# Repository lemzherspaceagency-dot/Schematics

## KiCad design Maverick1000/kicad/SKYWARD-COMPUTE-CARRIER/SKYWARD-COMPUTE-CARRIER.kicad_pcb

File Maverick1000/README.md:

# Maverick 1000 — SKYWARD-COMPUTE-CARRIER

**Frontier Innovations** | Internal codename: **SKYWARD** | Product: **Maverick 1000**
**Board:** SKYWARD-COMPUTE-CARRIER, **Rev A**, fabrication-readiness completion pass 2026-09-24

This is the main avionics/compute PCB for the Maverick 1000 autonomous
aerial robotics platform: a real, editable KiCad 7 project (not a rendering
or a mockup), generated end-to-end by the Python scripts in `python/` from
a single source-of-truth netlist/component list.

## Fabrication status: FABRICATION READY — full acceptance-gate audit passed (0 unconnected, 2 DRC violations, both understood/informational)

**Read `docs/FINAL_DESIGN_AUDIT.md` (Section 0i) before doing anything
else.** This project has been through many audit/completion passes,
most recently a full "perfect PCB" acceptance audit — not just checking
for 0 unrouted, but individually inspecting every remaining DRC entry,
auditing microvia manufacturability against real fab capability,
checking for duplicate/dead copper, and independently re-verifying
parity, zones, mechanics, file integrity, and manufacturing outputs.
That audit found and fixed two real, previously-hidden defects:

1. **Dead/dangling copper**, real not cosmetic: hundreds of leftover
   router artifacts (staircases of tiny segments, and one entire
   abandoned 55mm/4-via routing attempt) removed via KiCad's own
   connectivity engine, re-verified `0 unconnected` after every single
   deletion. DRC violations: **17 → 2**.
2. **Microvia manufacturability**, hidden because DRC has no
   aspect-ratio check: all 48 microvias (0.1mm laser-drilled) were
   spanning ~0.487mm dielectric gaps on a 1.6mm-thick board — a ~4.9:1
   aspect ratio, unbuildable by any real laser-HDI process despite "0
   DRC errors." Fixed by correcting the board thickness to 0.6mm to
   match a real, purchasable every-layer HDI stackup (1:1 aspect
   ratio) — no copper touched. See
   `manufacturing/stackup_and_fab_notes.md`.

Both fixes were verified, not assumed: connectivity re-checked via
KiCad's `CONNECTIVITY_DATA` API after every change (not just the
summary DRC count, which was independently confirmed reliable after an
early false-alarm from this session's own verification tooling was
traced to a bug in that tooling, not the board). Everything else —
parity, zone integrity, mechanical outline, file-integrity reopen test,
visual inspection, manufacturing-output regeneration — was
independently re-checked this round rather than assumed from prior
passes. **Every acceptance gate now passes on real, reproducible
checks.** Full breakdown, including what was checked and found NOT to
be a problem (duplicate vias that turned out to be intentional stacked
microvias; a set of duplicate-width tracks tested and found unsafe to
remove, left in place and documented), is in
`docs/FINAL_DESIGN_AUDIT.md` Section 0i.

**Current state, in one table** (see `docs/FINAL_DESIGN_AUDIT.md` for the
full breakdown):

| Metric | Value |
|---|---|
| Components / nets / connections | 118 / 100 / 469 (`verification/validate_output.txt`) |
| Netlist cross-check mismatches | 0 (`verification/netlist_cross_check_output.txt`) |
| Real DRC violations | **2**, both `lib_footprint_mismatch` (J1/J2, a documented 40-micron library/board row-spacing difference — see `docs/DF40C_FOOTPRINT_VERIFICATION.md`) — 0 clearance/geometry/hole errors, 0 unconnected_items (`verification/drc_report.txt`) |
| Unconnected items (real routing gap) | **0.** All 469 connections verified via KiCad's connectivity engine, re-checked after every change this round |
| Microvia manufacturability | **Verified.** 48 microvias, 1:1 aspect ratio at the corrected 0.6mm every-layer HDI stackup — see `manufacturing/stackup_and_fab_notes.md` |
| GND copper planes | Filled on all 4 layers (single multi-layer zone object), confirmed real, fully connected — 0 isolated islands |
| CM4 programming/recovery interface | Implemented — see `docs/PROGRAMMING_DEBUG_GUIDE.md` |
| U8 (EC25 modem) footprint | **Resolved** — real independently-sourced pad geometry, see `docs/EC25_FOOTPRINT_VERIFICATION.md` |
| Schematic/design-data/PCB parity | 0 mismatches (469/469), verified both directions |
| Manufacturing outputs | Gerbers, drill, CPL, BOM, STEP, ZIP — regenerated and independently verified against the current board |

**Communications subsystem**: a Quectel EC25 LTE Cat 4 modem (U8) provides
a high-bandwidth data link (live video, mapping/LiDAR data, telemetry,
mission data) to a ground station, kept entirely separate from ELRS
(which remains the sole flight command-and-control link). A USB2512B hub
(U7) shares the CM4's single USB2 port between the modem and the
pre-existing Terra payload high-bandwidth channel. See
`docs/COMMS_MODULE_DECISION.md` for the full selection rationale and
`docs/architecture.md` §7 for the data path and failsafe-independence
design.

**Programming/debug/recovery** (added this pass — see
`docs/PROGRAMMING_DEBUG_GUIDE.md` for full detail): a 3.3V UART debug
console (J10), CM4 boot-mode/reset controls (SW1/SW2), 4 power-rail test
points (TP1-4), and — the one genuinely missing piece this pass found and
fixed — a USB boot-mode mux (U10) and dedicated external USB connector
(J13) so `rpiboot`-based eMMC programming is physically possible at all.
Before this pass, the CM4's only USB2 port was permanently wired to the
internal hub with no path out to a host PC, which would have made the
board's compute module unprogrammable/unrecoverable after first flash.

## Opening this project

1. Install [KiCad](https://www.kicad.org/) 7.0 or newer (this project was
   built and audited against 7.0.11; a normal desktop install, not a
   headless one, is required for the next steps).
2. Copy this entire `Maverick1000` folder to your machine (paths inside
   the project are relative, so it works from anywhere).
3. Open `kicad/SKYWARD-COMPUTE-CARRIER/SKYWARD-COMPUTE-CARRIER.kicad_pro`.
4. The custom parts library (`SKYWARD_Custom`) resolves automatically via
   the project-local library tables — you do not need to add it manually.
5. Zones are already filled in the shipped `.kicad_pcb` (confirmed real
   this pass — see `docs/ROUTING_STATUS.md`) — but if you make any
   routing changes, re-fill (Edit > Fill All Zones, hotkey B) before
   re-exporting Gerbers.
6. **Routing is complete.** All 469 connections are routed — 0
   unconnected. If you make further design changes and introduce new
   unrouted nets, see `docs/ROUTING_STATUS.md` for the methodology
   that closed every gap this project ever had (place a trial via at
   the candidate escape point and check real DRC before concluding a
   net is unroutable — several "provably closed" conclusions in this
   project's history turned out to be wrong).
7. Re-run DRC (Inspect > Design Rules Checker) after routing changes, and
   re-run `python/refill_zones.py` before it — new copper compared
   against a stale zone fill produces phantom clearance violations that
   have nothing to do with real geometry (see `docs/ROUTING_STATUS.md`
   Update 12 for how this was found).

## Directory structure

```
Maverick1000/
├── kicad/
│   ├── SKYWARD-COMPUTE-CARRIER/     <- open THIS .kicad_pro in KiCad
│   │   ├── SKYWARD-COMPUTE-CARRIER.kicad_pro
│   │   ├── SKYWARD-COMPUTE-CARRIER.kicad_sch
│   │   ├── SKYWARD-COMPUTE-CARRIER.kicad_pcb
│   │   ├── SKYWARD-COMPUTE-CARRIER.kicad_dru  (custom fine-pitch clearance rules)
│   │   ├── sym-lib-table / fp-lib-table   (project-local, portable)
│   │   └── full.net                        (exported netlist, for verification)
│   └── libraries/
│       ├── symbols/SKYWARD_Custom.kicad_sym
│       └── footprints/SKYWARD_Custom.pretty/
├── python/             <- every generator script; re-run to regenerate the project
├── docs/                <- architecture, verification, audit, and status docs
├── bom/BOM.csv
├── manufacturing/       <- gerbers, drill, position file, previews, fab notes
└── verification/        <- raw DRC/netlist-cross-check/validate output (evidence, not summaries)
```

## What has been verified (with sources — see the individual documents)

- **Every real-part pinout used in this design has been cross-checked
  against authoritative sources** — not assumed from a similarly-named
  part, not invented. See `docs/COMPONENT_FOOTPRINT_VERIFICATION_CHECKLIST.md`
  for the consolidated table (13 of 15 active ICs/connectors fully
  verified pinout+footprint; the 2 exceptions are individually flagged,
  not hidden). Highlights from earlier passes: the BQ25792 charger was
  previously modeled as a fictional simplified part (real part is a
  29-pin WQFN — `docs/BQ25792_VERIFICATION.md`); the CM4 connector pin
  numbers were arbitrary rather than real (`docs/CM4_PIN_VERIFICATION.md`);
  the DF40C-100DS-0.4V connector footprint used the wrong pad-numbering
  scheme entirely (`docs/DF40C_FOOTPRINT_VERIFICATION.md`).
- **Netlist correctness**: every net cross-checked pin-for-pin between
  `python/design_data.py` (the source of truth) and KiCad's own exported
  netlist — zero mismatches (`verification/netlist_cross_check_output.txt`).
  `python/validate.py` passes clean: 118 components, 100 nets, 469
  connections, no shorts/orphans/duplicates
  (`verification/validate_output.txt`).
- **Real DRC was actually run** against the PCB (via KiCad's Python API,
  since this KiCad 7.0.11 install has no `kicad-cli pcb drc`/`sch erc`
  command — see `docs/ERC_STATUS.md`). This pass alone found and fixed
  6 more real bugs on top of the several found in earlier passes: a
  false-positive DRC-environment issue (109 spurious "footprint not
  found" warnings from an unset env var), a real footprint coordinate bug
  (BQ25792 pin 17), and three real bugs in this pass's own new
  two-layer auto-router (missing awareness of pre-existing copper, an
  asymmetric clearance formula, and missing via-to-via/via-to-track
  checks) — every one caught by re-running real DRC, not assumed away.
  See `docs/ERC_STATUS.md` and `docs/ROUTING_STATUS.md`.
- **Zone filling is confirmed real and working in this environment**,
  reversing an earlier finding that it segfaults unconditionally — see
  `docs/ROUTING_STATUS.md` for the re-test evidence and the explicit
  caveat that any future session should re-verify this before relying on
  it.
- **Real manufacturing outputs** — Gerber X2, Excellon drill, and CSV
  placement data — regenerated from the current board and independently
  verified (drill hole counts cross-checked exactly against real
  via/pad counts). See `manufacturing/stackup_and_fab_notes.md`.

## What is not done (ranked by severity — see `docs/FINAL_DESIGN_AUDIT.md`)

Routing is complete (0 of 469 connections unconnected — see
`docs/ROUTING_STATUS.md` Update 25). What remains is scoped narrower
than before:

1. Several dimensional assumptions remain unverified against manufacturer
   mechanical drawings (DF40C/DF13 exact pad pitch and size, BQ25792
   exposed-pad size, SIM holder footprint, USB hub crystal/bias values,
   and U10's SEL-pin polarity) — flagged explicitly in each verification
   document and in `docs/assumptions.md`, not silently assumed correct.
2. U8's real power consumption and the comms subsystem's exact mass
   contribution are not quantified against real datasheet/measured
   numbers — see `docs/COMMS_MODULE_DECISION.md`.
3. `Hirose_DF40C-100DS-0.4V` (J1/J2) reports a library-metadata mismatch
   in DRC (`lib_footprint_mismatch`, warning severity, non-functional —
   does not affect the fabricated copper) — see `verification/drc_report.txt`.

## Documentation index

- **`docs/FINAL_DESIGN_AUDIT.md`** — the top-level audit report: what was
  checked, what was found, what the fabrication-readiness verdict is and
  why. Start here.
- **`docs/COMPONENT_FOOTPRINT_VERIFICATION_CHECKLIST.md`** — consolidated
  per-part VERIFIED/APPROXIMATED/UNRESOLVED-BLOCKER status.
- **`docs/PROGRAMMING_DEBUG_GUIDE.md`** — how to connect a host PC for
  serial console access and CM4 eMMC programming/recovery, pin-by-pin,
  with exact tools and procedures.
- **`docs/USB_MUX_VERIFICATION.md`** — the U10 USB boot-mode mux: part
  selection, real pinout source, and what's not independently verified.
- **`docs/COMMS_MODULE_DECISION.md`** — the high-bandwidth comms module
  selection/integration decision: what was chosen, why, alternatives
  considered, and integration requirements.
- `docs/architecture.md` — system architecture, design decisions and why
  (§7 covers the comms subsystem data path and failsafe design)
- `docs/power_architecture.md` — battery/dock power topology in detail
- `docs/connector_pinouts.md` — every connector, pin-by-pin
- `docs/assumptions.md` — every assumption made and risk, ranked
- `docs/CM4_PIN_VERIFICATION.md`, `docs/BQ25792_VERIFICATION.md`,
  `docs/LM74610_VERIFICATION.md`, `docs/DF40C_FOOTPRINT_VERIFICATION.md`,
  `docs/OTHER_COMPONENTS_VERIFICATION.md` — per-component real-datasheet
  verification, with sources
- `docs/ROUTING_STATUS.md` — exact routing status, the real bugs found
  and fixed while extending it this pass, and what remains
- `docs/ERC_STATUS.md` — ERC/DRC methodology, results, and the bugs found
  as a direct result of actually running real checks
- `bom/BOM.csv` — full bill of materials with real manufacturer part numbers
- `manufacturing/stackup_and_fab_notes.md` — stackup, assembly, fab notes,
  manufacturing review findings
- `manufacturing/previews/` — rendered top/bottom/all-copper board
  previews, plus a real STEP 3D model for mechanical inspection in a CAD
  viewer
- `verification/` — raw, reproducible tool output (DRC report, netlist
  cross-check, validate.py) backing every number stated above
- `python/README.md` — how the generators work, how to re-run them

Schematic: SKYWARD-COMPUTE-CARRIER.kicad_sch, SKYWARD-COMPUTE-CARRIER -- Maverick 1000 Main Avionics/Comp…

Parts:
C1, C2, C27, C29, C36: 22uF; C_1210_3225Metric
C3, C7, C8, C10, C21, C35: 10uF; C_0805_2012Metric
C4: 22uF; C_0805_2012Metric
C5, C6, C9, C20: 1uF; C_0603_1608Metric
C11, C12, C13, C16, C17, C19, C22, C26, C28, C30, C38: 100nF; C_0402_1005Metric
C14, C15: 10uF; C_0603_1608Metric
C18, C34, C37: 10nF; C_0402_1005Metric
C31, C32: 18pF; C_0402_1005Metric
C33: 4.7nF; C_0402_1005Metric
D1, D2, D4: SMBJ24A; D_SMB
D3, D5, D7: SS34; D_SMA
F1, F2: 3A_PTC; Fuse_1206_3216Metric
F3: 1.5A_PTC; Fuse_1206_3216Metric
F4: 2A_PTC; Fuse_1206_3216Metric
J1: CM4_J1; Hirose_DF40C-100DS-0.4V
J2: CM4_J2; Hirose_DF40C-100DS-0.4V
J3: BATT_IN; JST_GH_SM02B-GHS-TB_1x02-1MP_P1.25mm_Horizontal
J4: DOCK; JST_GH_SM03B-GHS-TB_1x03-1MP_P1.25mm_Horizontal
J5: FC; JST_GH_SM06B-GHS-TB_1x06-1MP_P1.25mm_Horizontal
J6: GNSS; JST_GH_SM06B-GHS-TB_1x06-1MP_P1.25mm_Horizontal
J7: ELRS; JST_GH_SM04B-GHS-TB_1x04-1MP_P1.25mm_Horizontal
J8: TOF; JST_SH_SM05B-SRSS-TB_1x05-1MP_P1.00mm_Horizontal
J9: TERRA; Hirose_DF13-22DP-1.25V
J10: DEBUG; PinHeader_1x06_P2.54mm_Vertical
J11: SIM_TRAY; SIM_NanoSIM_6Pin_generic
J12: ANT_CELLULAR; U.FL_Hirose_U.FL-R-SMT-1_Vertical
J13: USB_BOOT; USB_Micro-B_Amphenol_10118194_Horizontal
JP1: XSHUT_SEL; SolderJumper-3_P1.3mm_Bridged12_Pad1.0x1.5mm
L1: 10uH; L_Coilcraft_XAL4020-XXX
L2: 2.2uH; L_Coilcraft_XAL4020-XXX
L3: 6.8uH; L_Coilcraft_XAL4020-XXX
LED1: STATUS; LED_0603_1608Metric
MH1, MH2, MH3, MH4: M2.5; MountingHole_2.7mm_M2.5
Q1, Q2, Q5, Q6: DMP2305U-7; SOT-23
R1, R30: 10.0k; R_0402_1005Metric
R2: 3.09k; R_0402_1005Metric
R3, R16: 5.6k; R_0402_1005Metric
R5, R7, R8, R9, R14, R15, R17, R18, R20, R21, R24, R25, R26, R27: 10k; R_0402_1005Metric
R6: 330; R_0603_1608Metric
R10, R11, R12, R13: 4.7k; R_0402_1005Metric
R19: 10; R_0402_1005Metric
R28: 12k; R_0402_1005Metric
R29: 21.0k; R_0402_1005Metric
RSH1, RSH2, RSH3: 10mOhm; R_1206_3216Metric
SW1: nRPIBOOT; SW_SPST_B3U-1000P
SW2: RUN; SW_SPST_B3U-1000P
TP1: VBAT_BUS; TestPoint_Pad_D1.5mm
TP2: +5V0; TestPoint_Pad_D1.5mm
TP3: +3V3; TestPoint_Pad_D1.5mm
TP4: GND; TestPoint_Pad_D1.5mm
U1, U2: LM74610QDGKRQ1; VSSOP-8_3.0x3.0mm_P0.65mm
U3: BQ25792RQMR; QFN-29_L4.0-W4.0-P0.40-BQ25792RQMR
U4, U9: TPS5430DDA; TI_SO-PowerPAD-8_ThermalVias
U5: AP2112K-3.3TRG1; SOT-23-5
U6: INA3221AIPW; TSSOP-16_4.4x5mm_P0.65mm
U7: USB2512B-AEZG-TR; QFN-36-1EP_6x6mm_P0.5mm_EP3.7x3.7mm
U8: EC25VFA-512-STD; LCC-132_EC25_verified
U10: FSUSB42MUX; MSOP-10_3x3mm_P0.5mm
Y1: 24MHz; Crystal_SMD_3225-4Pin_3.2x2.5mm

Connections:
5V0_PRE: L1.2, RSH3.1, U6.2 (IN+3)
5V0_SW: C18.1, D5.1 (K), L1.1, U4.8 (PH)
+3V3: C6.1, C19.1, C20.1, C38.1, J1.99 (+3V3), J7.2, J8.2, J10.2, JP1.1, R5.1, R7.1, R8.1, R9.1, R10.1, R11.1, R12.1, R13.1, R14.1, R15.1, R20.1, R21.1, R24.1, R25.1, R26.1, R27.1, TP3.1, U5.5 (VOUT), U6.4 (VS), U6.16 (VPU), U7.5 (VDDA33), U7.10 (VDDA33), U7.15 (VDD33), U7.23 (VDD33), U7.29 (VDDA33), U7.36 (VDDA33), U10.1 (VCC)
+5V0: C4.1, C5.1, C11.1, C12.1, C13.1, C14.1, C15.1, F4.1, J1.77 (+5V0), J1.79 (+5V0), J1.81 (+5V0), J1.83 (+5V0), J1.85 (+5V0), J1.87 (+5V0), J5.2, J6.2, R1.1, RSH3.2, TP2.1, U5.1 (VIN), U5.3 (EN), U6.1 (IN-3), U7.27 (VBUS_DET), U8.71 (USB_VBUS)
ACDRV1_GATE: R19.1, U3.11 (ACDRV1)
BATT_F: C1.1, C21.1, D1.1 (A1), F1.2, Q1.2 (S), U1.4 (ANODE), U3.18 (BATP), U3.22 (BAT), U3.23 (BAT)
BATT_IN: F1.1, J3.1
BOOT_5V: C18.2, U4.1 (BOOT)
BOOT_USB_DM: J13.2 (D-), U10.6 (HSD1-)
BOOT_USB_DP: J13.3 (D+), U10.7 (HSD1+)
BTST1: C22.1, U3.4 (BTST1)
CM4_USB_DM: J2.3 (CM4_USB_DM), U10.4 (D-)
CM4_USB_DP: J2.5 (CM4_USB_DP), U10.3 (D+)
DOCK_F: D3.2 (A), F3.2
DOCK_OK: C22.2, D3.1 (K), D4.1 (A1), Q5.2 (S), U3.9 (VAC1)
DOCK_PWR_RAW: F3.1, J4.1
EEPROM_nWP: J1.20 (EEPROM_nWP), R9.2
FB5V: R1.2, R2.1, U4.4 (VSENSE)
GATE_DRIVE: Q5.1 (G), Q6.1 (G), R19.2
GND: C1.2, C2.2, C3.2, C4.2, C5.2, C6.2, C7.2, C8.2, C9.2, C10.2, C11.2, C12.2, C13.2, C14.2, C15.2, C19.2, C20.2, C21.2, C26.2, C27.2, C28.2, C29.2, C30.2, C31.2, C32.2, C33.2, C34.2, C35.2, C36.2, C38.2, D1.2 (A2), D2.2 (A2), D4.2 (A2), D5.2 (A), D7.2 (A), J1.1 (GND), J1.2 (GND), J1.7 (GND), J1.8 (GND), J1.13 (GND), J1.14 (GND), J1.22 (GND), J1.23 (GND), J1.32 (GND), J1.33 (GND), J1.42 (GND), J1.43 (GND), J1.52 (GND), J1.53 (GND), J1.59 (GND), J1.60 (GND), J1.65 (GND), J1.66 (GND), J1.71 (GND), J1.74 (GND), J1.98 (GND), J2.1 (GND), J2.7 (GND), J2.8 (GND), J2.13 (GND), J2.14 (GND), J2.19 (GND), J2.20 (GND), J2.25 (GND), J2.26 (GND), J3.2, J4.2, J5.1, J6.1, J7.1, J8.1, J9.2 (GND), J9.3 (GND), J9.19 (GND), J10.1, J11.2, J12.2 (Ext), J13.5 (GND), J13.6 (Shield), LED1.2 (A), R2.2, R3.2, R16.2, R18.2, R28.2, R30.2, SW1.2, SW2.2, TP4.1, U3.8 (VAC2), U3.13 (~CE), U3.27 (GND), U3.30 (EP), U4.6 (GND), U4.9 (GNDPAD), U5.2 (GND), U6.3 (GND), U6.5 (A0), U7.37 (VSS_EP), U8.8 (GND), U8.9 (GND), U8.10 (USIM_GND), U8.19 (GND), U8.22 (GND), U8.36 (GND), U8.46 (GND), U8.48 (GND), U8.50 (GND), U8.51 (GND), U8.52 (GND), U8.53 (GND), U8.54 (GND), U8.56 (GND), U8.72 (GND), U8.85 (GND), U8.86 (GND), U8.87 (GND), U8.88 (GND), U8.89 (GND), U8.90 (GND), U8.91 (GND), U8.92 (GND), U8.93 (GND), U8.94 (GND), U8.95 (GND), U8.96 (GND), U8.97 (GND), U8.98 (GND), U8.99 (GND), U8.100 (GND), U8.101 (GND), U8.102 (GND), U8.103 (GND), U8.104 (GND), U8.105 (GND), U8.106 (GND), U8.107 (GND), U8.108 (GND), U8.109 (GND), U8.110 (GND), U8.111 (GND), U8.112 (GND), U9.6 (GND), U9.9 (GNDPAD), U10.5 (GND), U10.10 (~OE)
GPIO_CHG_INT: J1.24 (GPIO_CHG_INT), R21.2, U3.21 (~INT)
GPIO_DOCK_DET: J1.30 (GPIO_DOCK_DET), J4.3, R5.2
GPIO_FC_AUX: J1.47 (GPIO_FC_AUX), J5.6
GPIO_FC_RESET: J1.46 (GPIO_FC_RESET), J5.5
GPIO_GNSS_PPS: J1.29 (GPIO_GNSS_PPS), J6.5
GPIO_MODEM_PWRKEY: J1.37 (GPIO_MODEM_PWRKEY), U8.21 (PWRKEY)
GPIO_MODEM_RESET: J1.41 (GPIO_MODEM_RESET), U8.20 (RESET_N)
GPIO_STATUS_LED: J1.45 (GPIO_STATUS_LED), R6.1
GPIO_TERRA_A: J1.27 (GPIO_TERRA_A), J9.14 (TERRA_GPIO_A)
GPIO_TERRA_B: J1.25 (GPIO_TERRA_B), J9.15 (TERRA_GPIO_B)
GPIO_TERRA_IRQ: J1.49 (GPIO_TERRA_IRQ), J9.16 (TERRA_IRQ_N)
GPIO_TERRA_TRIG: J1.26 (GPIO_TERRA_TRIG), J9.17 (TERRA_TRIG)
GPIO_TOF_INT: J1.50 (GPIO_TOF_INT), J8.5
HUB_USB_DM: U7.30 (USBDM_UP), U10.8 (HSD2-)
HUB_USB_DP: U7.31 (USBDP_UP), U10.9 (HSD2+)
I2C0_SCL: J1.35 (I2C0_SCL), J8.4, R11.2, U3.14 (SCL), U6.6 (SCL)
I2C0_SDA: J1.36 (I2C0_SDA), J8.3, R10.2, U3.15 (SDA), U6.7 (SDA)
I2C1_SCL: J9.5 (TERRA_SCL), R13.2
I2C1_SDA: J9.4 (TERRA_SDA), R12.2
ILIM_SET: R3.1, U3.17 (ILIM_HIZ)
LED_A: LED1.1 (K), R6.2
MODEM_5V0_SW: C37.1, D7.1 (K), L3.1, U9.8 (PH)
MODEM_ANT_MAIN: J12.1 (In), U8.49 (ANT_MAIN)
MODEM_BOOT: C37.2, U9.1 (BOOT)
MODEM_FB: R29.2, R30.1, U9.4 (VSENSE)
MODEM_SIM_CLK: J11.4, U8.16 (USIM_CLK)
MODEM_SIM_DATA: J11.3, U8.15 (USIM_DATA)
MODEM_SIM_PRESENCE: J11.6, U8.13 (USIM_PRESENCE)
MODEM_SIM_RST: J11.5, U8.17 (USIM_RST)
MODEM_SIM_VDD: J11.1, U8.14 (USIM_VDD)
MODEM_USB_DM: U7.3 (USBDM_DN2), U8.70 (USB_DM)
MODEM_USB_DP: U7.4 (USBDP_DN2), U8.69 (USB_DP)
MODEM_VBAT: C26.1, C27.1, C28.1, C29.1, C36.1, L3.2, R29.1, U8.57 (VBAT_RF), U8.58 (VBAT_RF), U8.59 (VBAT_BB), U8.60 (VBAT_BB)
MODEM_W_DISABLE_N: R24.2, U8.4 (W_DISABLE#)
P1_F: C2.1, D2.1 (A1), F2.2, Q2.2 (S), U2.4 (ANODE)
PMID: C10.1, U3.29 (PMID)
PROG_SET: R16.1, U3.20 (PROG)
Q1_GATE: Q1.1 (G), U1.2 (GATE_PULL_DOWN), U1.6 (GATE_DRIVE)
Q2_GATE: Q2.1 (G), U2.2 (GATE_PULL_DOWN), U2.6 (GATE_DRIVE)
Q5_Q6_MID: Q5.3 (D), Q6.3 (D)
QON_N: R20.2, U3.12 (~QON)
REGN: C9.1, R17.1, U3.5 (REGN)
RUN_PG: J1.92 (RUN_PG), J10.6, R8.2, SW2.1
SPI0_CE0_N: J1.39 (SPI0_CE0_N), J9.9 (TERRA_CS_N)
SPI0_MISO: J1.40 (SPI0_MISO), J9.8 (TERRA_MISO)
SPI0_MOSI: J1.44 (SPI0_MOSI), J9.7 (TERRA_MOSI)
SPI0_SCLK: J1.38 (SPI0_SCLK), J9.6 (TERRA_SCLK)
SW1: L2.1, U3.28 (SW1)
SW2: L2.2, U3.26 (SW2)
SYS_NODE: C8.1, U3.25 (SYS)
TERRA_BATT_RAW: F2.1, J9.21 (TERRA_BATT_RAW), J9.22 (TERRA_BATT_RAW)
TERRA_PRESENCE_N: J9.18 (TERRA_PRESENCE_N), R14.2
TERRA_PWR: F4.2, J9.1 (TERRA_PWR), J9.20 (TERRA_PWR)
TS_BIAS: R17.2, R18.1, U3.16 (TS)
U7_CRFILT: C33.1, U7.14 (CRFILT)
U7_PLLFILT: C34.1, U7.34 (PLLFILT)
U7_RBIAS: R28.1, U7.35 (RBIAS)
U7_RESET_N: C30.1, R25.2, U7.26 (RESET_N)
U7_SCL: R27.2, U7.24 (SCL)
U7_SDA: R26.2, U7.22 (SDA)
U7_XTALIN: C31.1, U7.33 (XTALIN), Y1.1
U7_XTALOUT: C32.1, U7.32 (XTALOUT), Y1.2
UART0_RXD0: J1.51 (UART0_RXD0), J5.4, J10.4
UART0_TXD0: J1.55 (UART0_TXD0), J5.3, J10.3
UART3_RXD3: J1.34 (UART3_RXD3), J6.3
UART3_TXD3: J1.54 (UART3_TXD3), J6.4
UART5_RXD5: J1.28 (UART5_RXD5), J7.3
UART5_TXD5: J1.31 (UART5_TXD5), J7.4
USB2_0_DN: J9.13 (TERRA_USB_DN), U7.1 (USBDM_DN1)
USB2_0_DP: J9.12 (TERRA_USB_DP), U7.2 (USBDP_DN1)
VBAT_BUS: C3.1, C35.1, RSH1.2, RSH2.2, TP1.1, U4.5 (EN), U4.7 (VIN), U6.11 (IN-1), U6.14 (IN-2), U9.5 (EN), U9.7 (VIN)
VBAT_MAIN_OUT: Q1.3 (D), RSH1.1, U1.8 (CATHODE), U6.12 (IN+1)
VBAT_P1_OUT: Q2.3 (D), RSH2.1, U2.8 (CATHODE), U6.15 (IN+2)
VBUS_IN: C7.1, Q6.2 (S), U3.2 (VBUS), U3.3 (VBUS)
VCAP1_H: C16.2, U1.7 (VCAPH)
VCAP1_L: C16.1, U1.1 (VCAPL)
VCAP2_H: C17.2, U2.7 (VCAPH)
VCAP2_L: C17.1, U2.1 (VCAPL)
XSHUT: JP1.2, R15.2
nRPIBOOT: J1.93 (nRPIBOOT), J10.5, R7.2, SW1.1, U10.2 (SEL)

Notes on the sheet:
CM4 MODULE CONNECTORS
POWER: BATTERY INPUTS, ORING, REGULATION, CHARGING, TELEMETRY
CM4 SUPPORT: BOOT/RESET STRAPS, DECOUPLING, DEBUG HEADER
HIGH-BANDWIDTH COMMS: USB HUB, EC25 LTE MODEM, DEDICATED POWER
PERIPHERALS: FC / GNSS / ELRS / TOF / TERRA
TEST POINTS
MECHANICAL

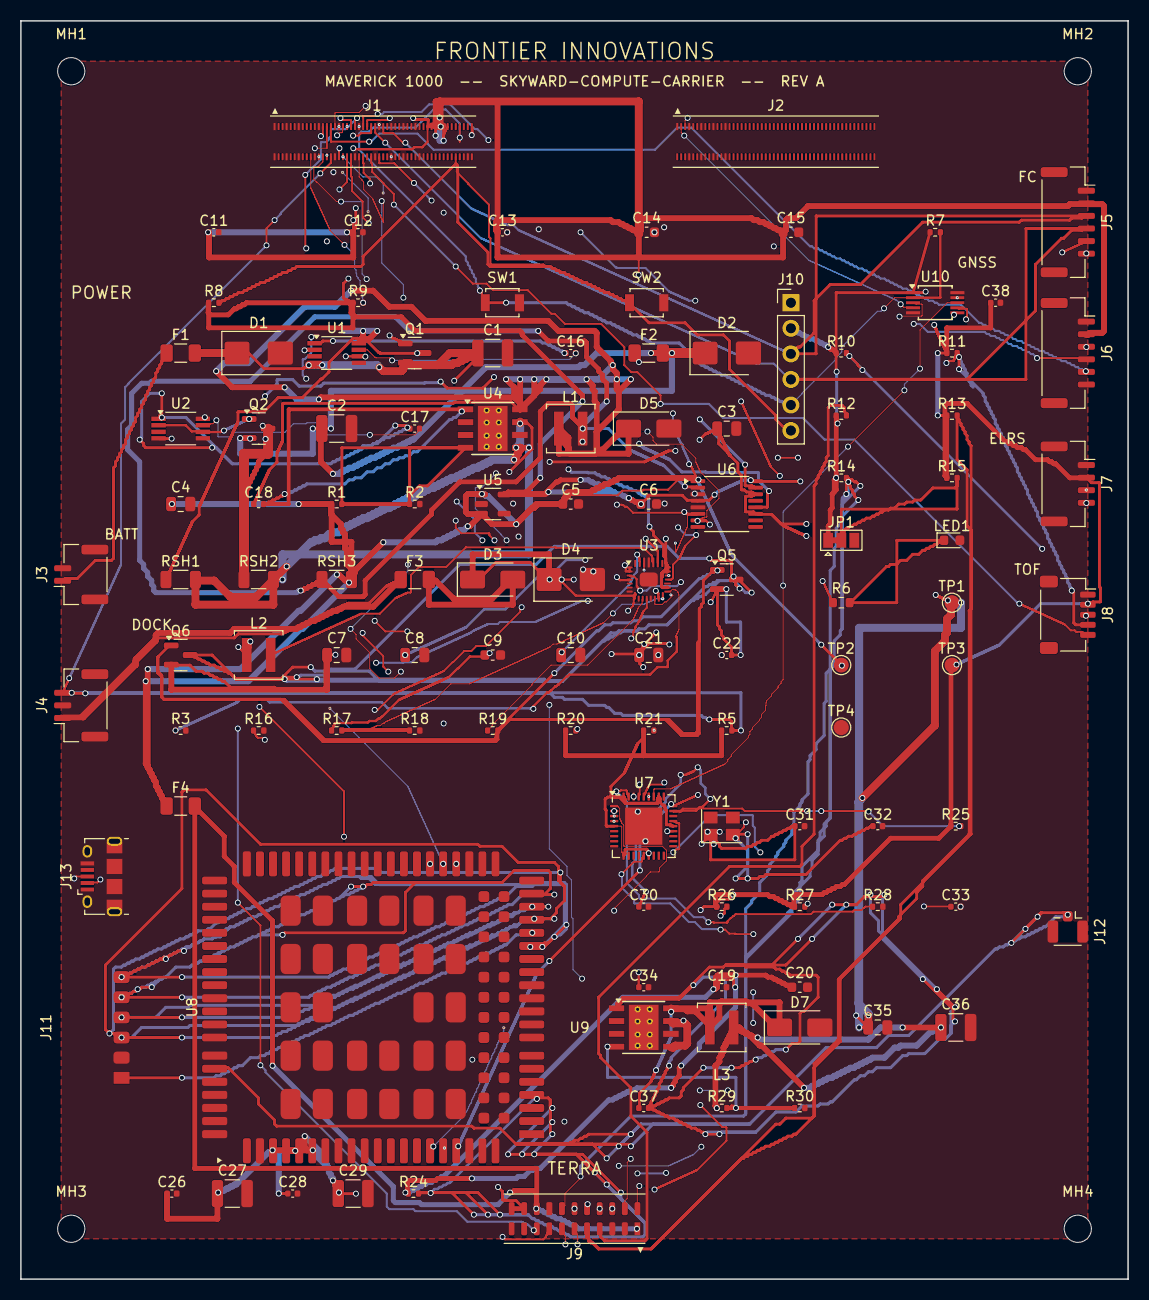
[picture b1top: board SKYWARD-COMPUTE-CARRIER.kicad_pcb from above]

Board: 4 copper layers, 110.0 x 125.0 mm, 118 parts (0 on the bottom side), 100 nets.

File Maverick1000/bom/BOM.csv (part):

Refs,Qty,Value,MPN,Manufacturer,Footprint,Description,Group
"C11, C12, C13",3,100nF,GRM155R71H104KE14D,Murata,Capacitor_SMD:C_0402_1005Metric,CM4 +5V0 decoupling,cm4
"C14, C15",2,10uF,GRM188R61A106KE69D,Murata,Capacitor_SMD:C_0603_1608Metric,CM4 +5V0 bulk decoupling,cm4
J1,1,CM4_J1,DF40C-100DS-0.4V(51),Hirose Electric,SKYWARD_Custom:Hirose_DF40C-100DS-0.4V,"100-pos 0.4mm SMD receptacle, CM4 primary connector (low/med-speed IO + power)",cm4
J10,1,DEBUG,PBC06SAAN,Sullins,Connector_PinHeader_2.54mm:PinHeader_1x06_P2.54mm_Vertical,CM4 UART console + boot/reset header,cm4
J2,1,CM4_J2,DF40C-100DS-0.4V(51),Hirose Electric,SKYWARD_Custom:Hirose_DF40C-100DS-0.4V,"100-pos 0.4mm SMD receptacle, CM4 secondary connector (high-speed IO + power)",cm4
R7,1,10k,RC0402FR-0710KL,Yageo,Resistor_SMD:R_0402_1005Metric,nRPIBOOT pull-up,cm4
R8,1,10k,RC0402FR-0710KL,Yageo,Resistor_SMD:R_0402_1005Metric,RUN_PG pull-up,cm4
R9,1,10k,RC0402FR-0710KL,Yageo,Resistor_SMD:R_0402_1005Metric,EEPROM_nWP pull-up (default: boot config write-protected),cm4
SW1,1,nRPIBOOT,B3U-1000P,Omron,Button_Switch_SMD:SW_SPST_B3U-1000P,"Tactile SW, hold to force CM4 USB boot mode",cm4
SW2,1,RUN,B3U-1000P,Omron,Button_Switch_SMD:SW_SPST_B3U-1000P,"Tactile SW, CM4 reset",cm4
C1,1,22uF,GRM32ER71V226KE15L,Murata,Capacitor_SMD:C_1210_3225Metric,Main battery input bulk cap,power
C10,1,10uF,GRM21BR61H106KE43L,Murata,Capacitor_SMD:C_0805_2012Metric,BQ25792 PMID decoupling,power
C16,1,100nF,GRM155R71H104KE14D,Murata,Capacitor_SMD:C_0402_1005Metric,U1 (LM74610) VCAP charge-pump cap,power
C17,1,100nF,GRM155R71H104KE14D,Murata,Capacitor_SMD:C_0402_1005Metric,U2 (LM74610) VCAP charge-pump cap,power
C18,1,10nF,GRM155R71H103KA88D,Murata,Capacitor_SMD:C_0402_1005Metric,5V buck BOOT bootstrap cap,power
C2,1,22uF,GRM32ER71V226KE15L,Murata,Capacitor_SMD:C_1210_3225Metric,Terra P1 input bulk cap,power
C21,1,10uF,GRM21BR61H106KE43L,Murata,Capacitor_SMD:C_0805_2012Metric,"BQ25792 BAT decoupling (at the charger, in addition to C1 at the ORing input)",power
C22,1,100nF,GRM155R71H103KA88D,Murata,Capacitor_SMD:C_0402_1005Metric,"BQ25792 BTST1 bootstrap cap -- HIGHEST-UNCERTAINTY connection on this board, see docs/BQ25792_VERIFICATION.md",power
C3,1,10uF,GRM21BR61H106KE43L,Murata,Capacitor_SMD:C_0805_2012Metric,5V buck input cap,power
C4,1,22uF,GRM21BR61A226ME44L,Murata,Capacitor_SMD:C_0805_2012Metric,5V buck output cap,power
C5,1,1uF,GRM188R61A105KA61D,Murata,Capacitor_SMD:C_0603_1608Metric,3V3 LDO input cap,power
C6,1,1uF,GRM188R61A105KA61D,Murata,Capacitor_SMD:C_0603_1608Metric,3V3 LDO output cap,power
C7,1,10uF,GRM21BR61H106KE43L,Murata,Capacitor_SMD:C_0805_2012Metric,BQ25792 VBUS input cap,power
C8,1,10uF,GRM21BR61H106KE43L,Murata,Capacitor_SMD:C_0805_2012Metric,BQ25792 SYS output cap,power
C9,1,1uF,GRM188R61A105KA61D,Murata,Capacitor_SMD:C_0603_1608Metric,BQ25792 REGN (internal LDO) decoupling,power
D1,1,SMBJ24A,SMBJ24A,Littelfuse,Diode_SMD:D_SMB,"Main battery input TVS clamp, 24V standoff",power
D2,1,SMBJ24A,SMBJ24A,Littelfuse,Diode_SMD:D_SMB,"Terra P1 input TVS clamp, 24V standoff",power
D3,1,SS34,SS34,Onsemi,Diode_SMD:D_SMA,Dock input reverse-polarity protection,power
D4,1,SMBJ24A,SMBJ24A,Littelfuse,Diode_SMD:D_SMB,Dock input TVS clamp,power
D5,1,SS34,SS34,Onsemi,Diode_SMD:D_SMA,"5V buck catch diode (PH->GND, non-synchronous TPS5430 topology)",power
F1,1,3A_PTC,1206L300/16DR,Bourns,Fuse:Fuse_1206_3216Metric,Main battery input resettable PTC fuse,power
F2,1,3A_PTC,1206L300/16DR,Bourns,Fuse:Fuse_1206_3216Metric,Terra P1 input resettable PTC fuse,power
F3,1,1.5A_PTC,1206L150/16DR,Bourns,Fuse:Fuse_1206_3216Metric,Dock charge input PTC fuse,power
F4,1,2A_PTC,1206L200/16DR,Bourns,Fuse:Fuse_1206_3216Metric,Terra TERRA_PWR independent fuse,power
J3,1,BATT_IN,SM02B-GHS-TB,JST,Connector_JST:JST_GH_SM02B-GHS-TB_1x02-1MP_P1.25mm_Horizontal,4S LiHV main battery low-current tap,power
J4,1,DOCK,SM03B-GHS-TB,JST,Connector_JST:JST_GH_SM03B-GHS-TB_1x03-1MP_P1.25mm_Horizontal,"Dock power + presence-detect, wired to skid contacts",power
L1,1,10uH,XAL4020-103MEB,Coilcraft,Inductor_SMD:L_Coilcraft_XAL4020-XXX,5V buck inductor,power
L2,1,2.2uH,XAL4020-222MEB,Coilcraft,Inductor_SMD:L_Coilcraft_XAL4020-XXX,"BQ25792 buck-boost inductor, SW1-SW2",power
Q1,1,DMP2305U-7,DMP2305U-7,Diodes Incorporated,Package_TO_SOT_SMD:SOT-23,"P-MOSFET, main battery ORing pass element",power
Q2,1,DMP2305U-7,DMP2305U-7,Diodes Incorporated,Package_TO_SOT_SMD:SOT-23,"P-MOSFET, Terra P1 ORing pass element",power
Q5,1,DMP2305U-7,DMP2305U-7,Diodes Incorporated,Package_TO_SOT_SMD:SOT-23,"BQ25792 input blocking FET, ACFET1 (back-to-back pair with Q6)",power
Q6,1,DMP2305U-7,DMP2305U-7,Diodes Incorporated,Package_TO_SOT_SMD:SOT-23,"BQ25792 input blocking FET, RBFET1 (back-to-back pair with Q5)",power
R1,1,10.0k,RC0402FR-0710KL,Yageo,Resistor_SMD:R_0402_1005Metric,5V buck FB divider top,power
R16,1,5.6k,RC0402FR-075K6L,Yageo,Resistor_SMD:R_0402_1005Metric,"BQ25792 PROG resistor -- value TBD, confirm against datasheet equation",power
R17,1,10k,RC0402FR-0710KL,Yageo,Resistor_SMD:R_0402_1005Metric,BQ25792 TS bias divider (upper) -- approximates room temp; replace with real NTC divider if the battery pack provides a thermistor lead,power
R18,1,10k,RC0402FR-0710KL,Yageo,Resistor_SMD:R_0402_1005Metric,BQ25792 TS bias divider (lower),power
R19,1,10,RC0402FR-0710RL,Yageo,Resistor_SMD:R_0402_1005Metric,BQ25792 ACDRV1 gate series resistor (Q5/Q6),power
R2,1,3.09k,RC0402FR-073K09L,Yageo,Resistor_SMD:R_0402_1005Metric,5V buck FB divider bottom,power
R20,1,10k,RC0402FR-0710KL,Yageo,Resistor_SMD:R_0402_1005Metric,"BQ25792 QON pull-up (inactive default, no manual power button in Rev A)",power
R21,1,10k,RC0402FR-0710KL,Yageo,Resistor_SMD:R_0402_1005Metric,BQ25792 INT open-drain pull-up,power
R3,1,5.6k,RC0402FR-075K6L,Yageo,Resistor_SMD:R_0402_1005Metric,"BQ25792 ILIM_HIZ set resistor -- value TBD, confirm against datasheet equation",power
R5,1,10k,RC0402FR-0710KL,Yageo,Resistor_SMD:R_0402_1005Metric,GPIO_DOCK_DET pull-up (dock presence detect),power
RSH1,1,10mOhm,WSL1206R0100FEA,Vishay,Resistor_SMD:R_1206_3216Metric,Main battery current shunt,power
RSH2,1,10mOhm,WSL1206R0100FEA,Vishay,Resistor_SMD:R_1206_3216Metric,Terra P1 current shunt,power
RSH3,1,10mOhm,WSL1206R0100FEA,Vishay,Resistor_SMD:R_1206_3216Metric,+5V0 CM4 rail current shunt,power
U1,1,LM74610QDGKRQ1,LM74610QDGKRQ1,Texas Instruments,Package_SO:VSSOP-8_3.0x3.0mm_P0.65mm,"Ideal-diode ORing controller, main battery",power
U2,1,LM74610QDGKRQ1,LM74610QDGKRQ1,Texas Instruments,Package_SO:VSSOP-8_3.0x3.0mm_P0.65mm,"Ideal-diode ORing controller, Terra P1",power
U3,1,BQ25792RQMR,BQ25792RQMR,Texas Instruments,SKYWARD_Custom:QFN-29_L4.0-W4.0-P0.40-BQ25792RQMR,"1-4S I2C buck-boost charger, dock -> main battery",power
U4,1,TPS5430DDA,TPS5430DDA,Texas Instruments,Package_SO:TI_SO-PowerPAD-8_ThermalVias,"3A non-sync buck, 5.5-36V in, adjustable -> set for +5V0",power
U5,1,AP2112K-3.3TRG1,AP2112K-3.3TRG1,Diodes Inc.,Package_TO_SOT_SMD:SOT-23-5,"600mA LDO, +5V0 -> +3V3 (low-noise, GNSS-friendly)",power
U6,1,INA3221AIPW,INA3221AIPW,Texas Instruments,Package_SO:TSSOP-16_4.4x5mm_P0.65mm,"3-ch I2C V/I monitor: main batt, P1 batt, +5V0",power
J5,1,FC,SM06B-GHS-TB,JST,Connector_JST:JST_GH_SM06B-GHS-TB_1x06-1MP_P1.25mm_Horizontal,Flight controller UART/telemetry link,periph
J6,1,GNSS,SM06B-GHS-TB,JST,Connector_JST:JST_GH_SM06B-GHS-TB_1x06-1MP_P1.25mm_Horizontal,BN-220 GNSS UART + PPS,periph
J7,1,ELRS,SM04B-GHS-TB,JST,Connector_JST:JST_GH_SM04B-GHS-TB_1x04-1MP_P1.25mm_Horizontal,ELRS receiver UART,periph
J8,1,TOF,SM05B-SRSS-TB,JST,Connector_JST:JST_SH_SM05B-SRSS-TB_1x05-1MP_P1.00mm_Horizontal,VL53L5CX-SATEL I2C + power,periph
J9,1,TERRA,DF13-22DP-1.25V,Hirose Electric,SKYWARD_Custom:Hirose_DF13-22DP-1.25V,Standardized Terra payload bus,periph
JP1,1,XSHUT_SEL,-,-,Jumper:SolderJumper-3_P1.3mm_Bridged12_Pad1.0x1.5mm,VL53L5CX XSHUT source select: free-run (default) vs CM4 GPIO,periph
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
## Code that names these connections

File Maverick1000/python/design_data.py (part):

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    Component("R21", "Device:R", "Resistor_SMD:R_0402_1005Metric",
               "10k", "RC0402FR-0710KL", "Yageo", "BQ25792 INT open-drain pull-up", group="power"),
    Component("R5", "Device:R", "Resistor_SMD:R_0402_1005Metric",
               "10k", "RC0402FR-0710KL", "Yageo", "GPIO_DOCK_DET pull-up (dock presence detect)", group="power"),

    # ---- Terra payload fuse & pull-ups ------------------------------------------------
    Component("F4", "Device:Fuse", "Fuse:Fuse_1206_3216Metric",
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    Component("R15", "Device:R", "Resistor_SMD:R_0402_1005Metric",
               "10k", "RC0402FR-0710KL", "Yageo", "VL53L5CX XSHUT default pull-up (solder-jumper option, see JP1)", group="periph"),
    Component("JP1", "Connector_Generic:Conn_01x03", "Jumper:SolderJumper-3_P1.3mm_Bridged12_Pad1.0x1.5mm",
               "XSHUT_SEL", "-", "-", "VL53L5CX XSHUT source select: free-run (default) vs CM4 GPIO", group="periph", footprint_group="jumper"),

    # ---- Peripheral connectors --------------------------------------------------------
    Component("J5", "Connector_Generic:Conn_01x06", "Connector_JST:JST_GH_SM06B-GHS-TB_1x06-1MP_P1.25mm_Horizontal",
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    # U9 + L3 + D6 + support passives: a second TPS5430 buck stage
    # (same real, already-verified part and non-synchronous-with-catch-
    # diode topology as U4's +5V0 rail, see docs/OTHER_COMPONENTS_
    # VERIFICATION.md) feeding U8's VBAT_BB/VBAT_RF pins from VBAT_BUS at
    # ~3.8V, sized within the 3.3-4.3V class typical for this module
    # family. A dedicated regulator (not the shared +3V3 logic rail) is
    # used specifically so a cellular TX current burst cannot dip the
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    1: "GND", 2: "GND", 7: "GND", 8: "GND", 13: "GND", 14: "GND",
    20: "EEPROM_nWP",
    22: "GND", 23: "GND",
    25: "GPIO_TERRA_B", 26: "GPIO_TERRA_TRIG", 27: "GPIO_TERRA_A",
    28: "UART5_RXD5", 29: "GPIO_GNSS_PPS", 30: "GPIO_DOCK_DET", 31: "UART5_TXD5",
    32: "GND", 33: "GND",
    34: "UART3_RXD3",
    35: "I2C0_SCL", 36: "I2C0_SDA",
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    # repurposed this pass for the comms module: a genuinely useful function
    # for a previously-idle, already-verified real pin, rather than
    # inventing a new/unverified GPIO number.
    37: "GPIO_MODEM_PWRKEY",  # GPIO7 -> U8 (EC25) PWRKEY
    38: "SPI0_SCLK", 39: "SPI0_CE0_N", 40: "SPI0_MISO",
    41: "GPIO_MODEM_RESET",  # GPIO25, same repurposing rationale -> U8 RESET_N
    42: "GND", 43: "GND",
    44: "SPI0_MOSI", 45: "GPIO_STATUS_LED", 46: "GPIO_FC_RESET", 47: "GPIO_FC_AUX",
    49: "GPIO_TERRA_IRQ", 50: "GPIO_TOF_INT", 51: "UART0_RXD0",
    52: "GND", 53: "GND",
    54: "UART3_TXD3", 55: "UART0_TXD0",
    59: "GND", 60: "GND",
    65: "GND", 66: "GND",
    71: "GND", 74: "GND",
    77: "+5V0", 79: "+5V0", 81: "+5V0", 83: "+5V0", 85: "+5V0", 87: "+5V0",
    24: "GPIO_CHG_INT",  # GPIO26, BQ25792 charge-fault interrupt
    92: "RUN_PG", 93: "nRPIBOOT",
    98: "GND", 99: "+3V3",  # GLOBAL_EN, tied high for normal always-enabled operation
}
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    25: "GND", 26: "GND",
}
# GPIO7 and GPIO25 (formerly documented real-but-unused SPI0-adjacent
# pins) are now used by the comms module (GPIO_MODEM_PWRKEY/_RESET above)
# -- no remaining placeholder nets in this design.
_CM4_PLACEHOLDER_NETS: tuple[str, ...] = ()

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# ANODE and CATHODE -- and its charge-pump cap goes BETWEEN VCAPL/VCAPH,
# not to ground. This replaced an earlier, incorrect 6-pin SOT-23-6 model
# with an invented GND pin. GATE_PULL_DOWN is tied to the same node as
# GATE_DRIVE (documented assumption -- both pins are involved in gate
# control per the part's naming; not independently confirmed from primary
# datasheet text, see the verification doc).
#
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# confirmed from primary datasheet text -- see the verification doc).
_add("DOCK_PWR_RAW", "J4", 1)
_add("GND", "J4", 2)
_add("GPIO_DOCK_DET", "J4", 3)     # shorted to GND by dock contact when seated
_add("+3V3", "R5", 1)
_add("GPIO_DOCK_DET", "R5", 2)
_add("DOCK_PWR_RAW", "F3", 1)
_add("DOCK_F", "F3", 2)
_add("DOCK_OK", "D3", 1)     # Schottky cathode (downstream, protected side)
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# highest-uncertainty analog circuit on this board -- see
# docs/BQ25792_VERIFICATION.md and docs/FINAL_DESIGN_AUDIT.md.
_add("DOCK_OK", "U3", 9)      # VAC1 (sense)
_add("DOCK_OK", "Q5", 2)      # Q5 source (P-FET, S per Device:Q_PMOS_GSD pin2)
_add("Q5_Q6_MID", "Q5", 3)    # Q5 drain
_add("Q5_Q6_MID", "Q6", 3)    # Q6 drain (back-to-back: drains tied)
_add("VBUS_IN", "Q6", 2)      # Q6 source -> BQ25792 VBUS pins
_add("ACDRV1_GATE", "U3", 11)  # ACDRV1
_add("ACDRV1_GATE", "R19", 1)
_add("GATE_DRIVE", "R19", 2)
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_add("BTST1", "U3", 4)
_add("BTST1", "C22", 1)
_add("DOCK_OK", "C22", 2)     # bootstrap cap referenced to the input rail (see audit note)
_add("VBUS_IN", "U3", 2); _add("VBUS_IN", "U3", 3)   # VBUS (both pins)
_add("VBUS_IN", "C7", 1); _add("GND", "C7", 2)  # input cap sits after the blocking FETs, on VBUS_IN

# unused second input (VAC2) tied to GND per TI convention for an
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_add("I2C0_SDA", "U3", 15)

# charge-fault interrupt -> CM4 GPIO26
_add("+3V3", "R21", 1); _add("GPIO_CHG_INT", "R21", 2)
_add("GPIO_CHG_INT", "U3", 21)  # ~INT

# TS: fixed bias divider approximating room temperature (documented
# placeholder -- replace with the pack's real NTC divider if available)
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# node, upstream of the Q1 ORing FET.
_add("SYS_NODE", "U3", 25)
_add("SYS_NODE", "C8", 1); _add("GND", "C8", 2)
_add("BATT_F", "U3", 22); _add("BATT_F", "U3", 23)   # BAT (both pins)
_add("BATT_F", "C21", 1); _add("GND", "C21", 2)

_add("GND", "U3", 27)         # GND pin
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# --- FC / GNSS / ELRS / TOF connectors -----------------------------------------
_add("GND", "J5", 1); _add("+5V0", "J5", 2)
_add("UART0_TXD0", "J5", 3); _add("UART0_RXD0", "J5", 4)
_add("GPIO_FC_RESET", "J5", 5); _add("GPIO_FC_AUX", "J5", 6)

_add("GND", "J6", 1); _add("+5V0", "J6", 2)
_add("UART3_RXD3", "J6", 3)     # GNSS TX -> CM4 RX
_add("UART3_TXD3", "J6", 4)     # CM4 TX -> GNSS RX
_add("GPIO_GNSS_PPS", "J6", 5)
# J_GNSS pin 6: reserved, NC

_add("GND", "J7", 1); _add("+3V3", "J7", 2)
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
_add("GND", "J8", 1); _add("+3V3", "J8", 2)
_add("I2C0_SDA", "J8", 3); _add("I2C0_SCL", "J8", 4)
_add("GPIO_TOF_INT", "J8", 5)

_add("+3V3", "R10", 1); _add("I2C0_SDA", "R10", 2)
_add("+3V3", "R11", 1); _add("I2C0_SCL", "R11", 2)
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
_add("+3V3", "JP1", 1)      # default bridge 1-2: XSHUT free-run, pulled high
_add("XSHUT", "JP1", 2)
# JP1 pin 3 (alternative: bridge 2-3 for future CM4 GPIO control of XSHUT) is
# intentionally reserved/unpopulated in Rev A -- no-connect flagged, not wired
# to a CM4 pin, per docs/assumptions.md #6.
_add("+3V3", "R15", 1); _add("XSHUT", "R15", 2)
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# allocated to FC/GNSS/ELRS. See docs/CM4_PIN_VERIFICATION.md.
_add("USB2_0_DP", "J9", 12)
_add("USB2_0_DN", "J9", 13)
_add("GPIO_TERRA_A", "J9", 14)
_add("GPIO_TERRA_B", "J9", 15)
_add("GPIO_TERRA_IRQ", "J9", 16)
_add("GPIO_TERRA_TRIG", "J9", 17)
_add("TERRA_PRESENCE_N", "J9", 18)
_add("GND", "J9", 19)
_add("TERRA_PWR", "J9", 20)
_add("+3V3", "R14", 1); _add("TERRA_PRESENCE_N", "R14", 2)

# --- Status LED --------------------------------------------------------------------
_add("GPIO_STATUS_LED", "R6", 1)
_add("LED_A", "R6", 2)
_add("LED_A", "LED1", 1)
_add("GND", "LED1", 2)
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# sits between them so the same pair can reach either U7 (normal
# operation) or J13 (external boot/recovery connector), selected by the
# same nRPIBOOT signal that already puts the CM4 into USB boot mode.
_add("CM4_USB_DP", "U10", 3)    # D+ (common) -- J2 pin 5 already ties into this net via CM4_J2_PINS above
_add("CM4_USB_DM", "U10", 4)    # D- (common)
_add("+3V3", "U10", 1)          # VCC
_add("+3V3", "C38", 1); _add("GND", "C38", 2)
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# regulated rail (MODEM_VBAT, from U9 below), consistent with common
# reference designs for this module class.
for _p in (59, 60):
    _add("MODEM_VBAT", "U8", _p)      # VBAT_BB x2 (dual-bonded pin)
for _p in (57, 58):
    _add("MODEM_VBAT", "U8", _p)      # VBAT_RF x2 (dual-bonded pin)
_add("MODEM_VBAT", "C26", 1); _add("GND", "C26", 2)
_add("MODEM_VBAT", "C27", 1); _add("GND", "C27", 2)
_add("MODEM_VBAT", "C28", 1); _add("GND", "C28", 2)
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# U8 power-on/reset control -- routed to the two CM4 GPIOs freed up by the
# GPIO7/GPIO25 repurposing above (real, previously-verified-spare pins,
# not invented ones)
_add("GPIO_MODEM_PWRKEY", "U8", 21)
_add("GPIO_MODEM_RESET", "U8", 20)
# STATUS (61) and NET_STATUS (6) intentionally left unconnected -- host-
# side link/network-registration monitoring is handled in software over
# the USB link itself (standard ModemManager/AT-command practice), making
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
